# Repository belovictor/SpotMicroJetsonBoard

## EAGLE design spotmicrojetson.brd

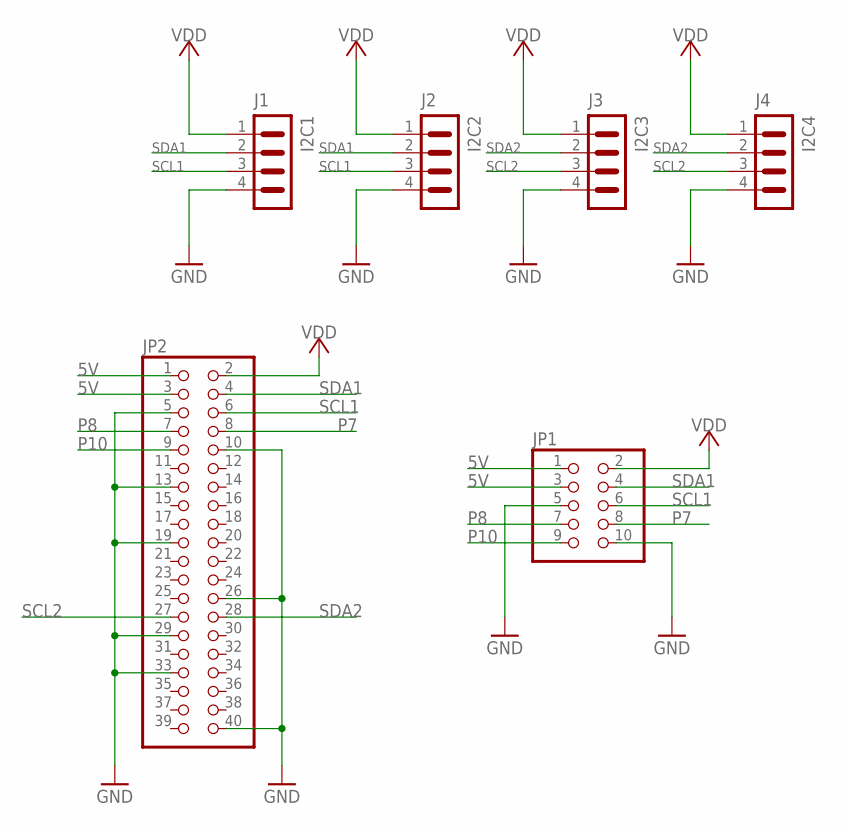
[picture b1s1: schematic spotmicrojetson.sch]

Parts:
J1: I2C1; CON_JST_B4B-PH-SM4-TB(LF)(SN)
J2: I2C2; CON_JST_B4B-PH-SM4-TB(LF)(SN)
J3: I2C3; CON_JST_B4B-PH-SM4-TB(LF)(SN)
J4: I2C4; CON_JST_B4B-PH-SM4-TB(LF)(SN)
JP1: PINHD-2X5SMT; 2X05_SMT
JP2: PINHD-2X20SMT; 2X20_SMT

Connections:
5V: JP1.1, JP1.3, JP2.1, JP2.3
GND: J1.4, J2.4, J3.4, J4.4, JP1.5, JP1.10, JP2.5, JP2.10, JP2.13, JP2.19, JP2.26, JP2.29, JP2.33, JP2.40
P7: JP1.8, JP2.8
P8: JP1.7, JP2.7
P10: JP1.9, JP2.9
SCL1: J1.3, J2.3, JP1.6, JP2.6
SCL2: J3.3, J4.3, JP2.27
SDA1: J1.2, J2.2, JP1.4, JP2.4
SDA2: J3.2, J4.2, JP2.28
VDD: J1.1, J2.1, J3.1, J4.1, JP1.2, JP2.2

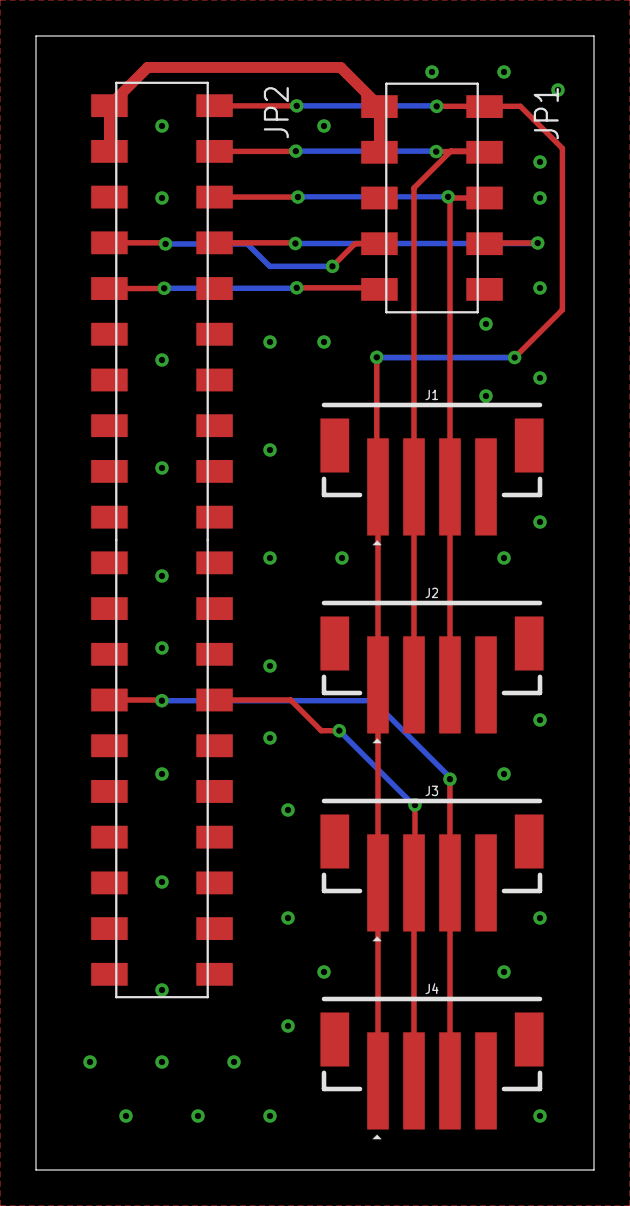
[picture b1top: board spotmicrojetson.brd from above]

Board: 2 copper layers, 31.0 x 63.0 mm, 6 parts (0 on the bottom side), 10 nets.

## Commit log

2022-02-06 Fix ground plane polygons
2022-02-06 Optimize layout
